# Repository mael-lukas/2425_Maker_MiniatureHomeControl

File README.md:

Miniature Home control

Maker 2024-2025 - Miniature Home control
========================================

Project overview

Introduction
------------

This project was carried out as part of the Maker option at ENSEA. The idea was to create a miniature home that could house a small animal with a bunch of actuated parts  
(doors, lights, food dispenser...) that could be activated remotely.  
Design-wise the house is inspired by typical doll house designs and modern houses:

Below is the architectural diagram that sums up all the features that were to be included in the house at the start of the project:

CAD
---

This project involved a lot of CAD. A significant part was the modeling of the whole house. The goal was to make the house out of wood using the laser cutter.  
Thus the model needed to be able to be separated in several parts to be cut on a flat sheet

All the furnitures to be placed in the house were also 3D modeled by myself (except the chair I downloaded it online). They were then 3D printed.

PCB
---

Every PCBs in this project were designed on KiCAD and manufactured by JLCPCB.  
This project needed two PCBs: one main unit would be wired to every actuatable parts in the house.  
Thus, it is mainly comprised of sockets to wire to every motors, lights, TV...

The second PCB is the controller of the house to actuate remotely every part of the house. Thus it is mainly comprised of buttons to look like a run-of-the-mill remote:

Assembly
--------

After laser cutting the wood the house was assembled, some furnitures were also placed inside:

The assembly part also involved a lot of wiring. I made custom wires for the power supply to power the main unit, a LiPo battery for the controller  
and several wires for motors and lights in the house:

Programming
-----------

The code was written  in C language on STM32 CubeIDE. It is devised according to this diagram:

I wrote a working code for the LCD screen (for the TV), servo motors, Neopixel LEDs and the MP3 module. I did not have time to test the code for the HC-05 bluetooth module.  
The whole code can be found in the GitHub repository (as well as every other resources of the project)

Final word
----------

I did not have the time to finish the project so only the house, the PCBs and the lights and doors are implemented but I still had a great time doing this project and participating in Maker.

### Short video

Here is a short [video](https://www.youtube.com/watch?v=WIeOZKU2mvY&t=1s) (in French) to sum up the project and my views on the Maker option

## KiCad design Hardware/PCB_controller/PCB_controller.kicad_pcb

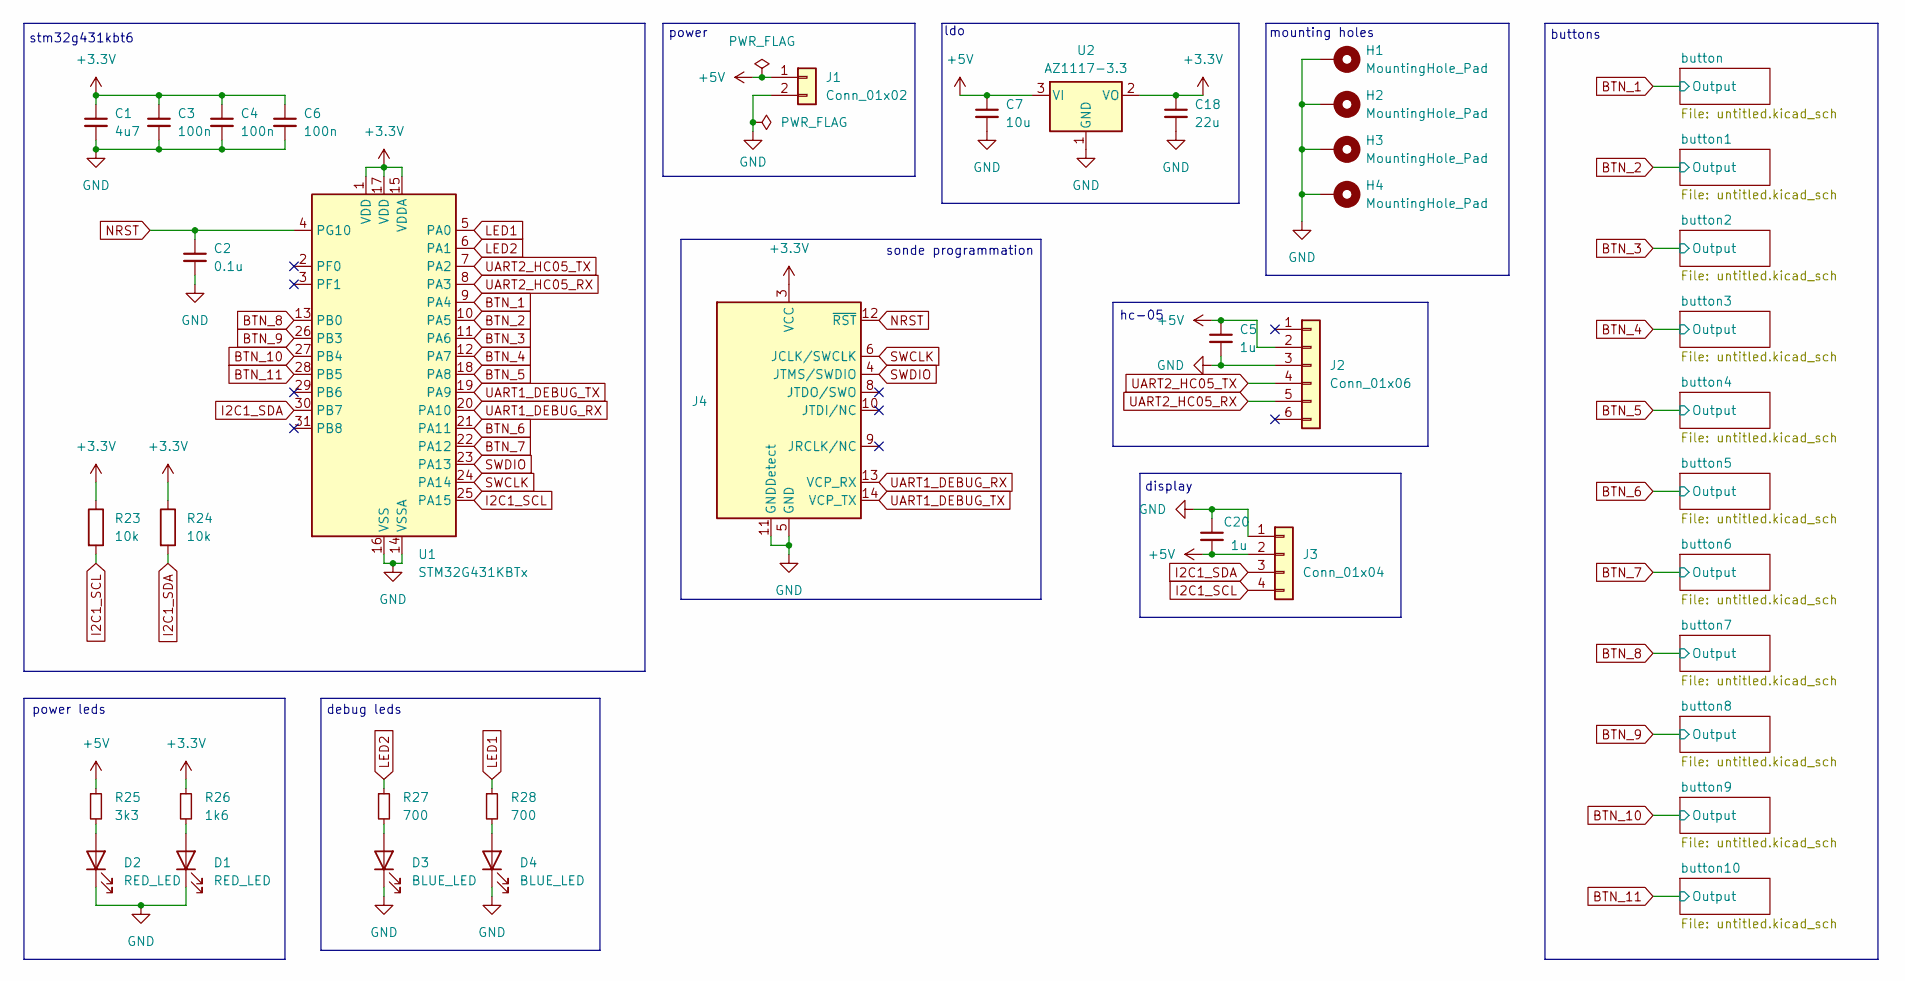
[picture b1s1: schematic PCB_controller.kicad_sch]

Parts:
C1: 4u7; C_0603_1608Metric
C2: 0.1u; C_0402_1005Metric_Pad0.74x0.62mm_HandSolder
C3, C4, C6: 100n; C_0402_1005Metric_Pad0.74x0.62mm_HandSolder
C5, C20: 1u; C_0603_1608Metric
C7: 10u; C_0603_1608Metric
C18: 22u; C_Elec_5x5.4
D1, D2: RED_LED; LED_0603_1608Metric; MPN 150060RS55040
D3, D4: BLUE_LED; LED_0603_1608Metric; MPN 150060BS55040
H1, H2, H3, H4: MountingHole_Pad; MountingHole_3.2mm_M3_Pad_Via
J1: Conn_01x02; JST_EH_B2B-EH-A_1x02_P2.50mm_Vertical
J2: Conn_01x06; JST_EH_B6B-EH-A_1x06_P2.50mm_Vertical
J3: Conn_01x04; JST_EH_B4B-EH-A_1x04_P2.50mm_Vertical
J4: Conn_ST_STDC14; PinHeader_2x07_P1.27mm_Vertical_SMD
R23, R24: 10k; R_0402_1005Metric_Pad0.72x0.64mm_HandSolder
R25: 3k3; R_0402_1005Metric_Pad0.72x0.64mm_HandSolder
R26: 1k6; R_0402_1005Metric_Pad0.72x0.64mm_HandSolder
R27, R28: 700; R_0402_1005Metric_Pad0.72x0.64mm_HandSolder
U1: STM32G431KBTx; LQFP-32_7x7mm_P0.8mm
U2: AZ1117-3.3; SOT-223-3_TabPin2; MPN AZ1117CH2-3.3TRG1

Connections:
+3.3V: C1.1, C3.1, C4.1, C6.1, C18.1, J4.3 (VCC), R23.1, R24.1, R26.1, U1.1 (VDD), U1.15 (VDDA), U1.17 (VDD), U2.2 (VO); also elsewhere on the board
+5V: C5.1, C7.1, C20.2, J1.1, J2.2, J3.2, R25.1, U2.3 (VI)
BTN_1: U1.9 (PA4); also elsewhere on the board
BTN_2: U1.10 (PA5); also elsewhere on the board
BTN_3: U1.11 (PA6); also elsewhere on the board
BTN_4: U1.12 (PA7); also elsewhere on the board
BTN_5: U1.18 (PA8); also elsewhere on the board
BTN_6: U1.21 (PA11); also elsewhere on the board
BTN_7: U1.22 (PA12); also elsewhere on the board
BTN_8: U1.13 (PB0); also elsewhere on the board
BTN_9: U1.26 (PB3); also elsewhere on the board
BTN_10: U1.27 (PB4); also elsewhere on the board
BTN_11: U1.28 (PB5); also elsewhere on the board
GND: C1.2, C2.2, C3.2, C4.2, C5.2, C6.2, C7.2, C18.2, C20.1, D1.1 (K), D2.1 (K), D3.1 (K), D4.1 (K), H1.1, H2.1, H3.1, H4.1, J1.2, J2.3, J3.1, J4.5 (GND), J4.7 (GND), J4.11 (GNDDetect), U1.14 (VSSA), U1.16 (VSS), U1.32 (VSS), U2.1 (GND); also elsewhere on the board
I2C1_SCL: J3.4, R23.2, U1.25 (PA15)
I2C1_SDA: J3.3, R24.2, U1.30 (PB7)
LED1: R28.1, U1.5 (PA0)
LED2: R27.1, U1.6 (PA1)
NRST: C2.1, J4.12 (~RST), U1.4 (PG10)
unnamed: D1.2 (A), R26.2
unnamed: D2.2 (A), R25.2
unnamed: D3.2 (A), R27.2
unnamed: D4.2 (A), R28.2
SWCLK: J4.6 (JCLK/SWCLK), U1.24 (PA14)
SWDIO: J4.4 (JTMS/SWDIO), U1.23 (PA13)
UART1_DEBUG_RX: J4.13 (VCP_RX), U1.20 (PA10)
UART1_DEBUG_TX: J4.14 (VCP_TX), U1.19 (PA9)
UART2_HC05_RX: J2.5, U1.8 (PA3)
UART2_HC05_TX: J2.4, U1.7 (PA2)

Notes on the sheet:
mounting holes
ldo
buttons
stm32g431kbt6
power
sonde programmation
debug leds
display
power leds
hc-05

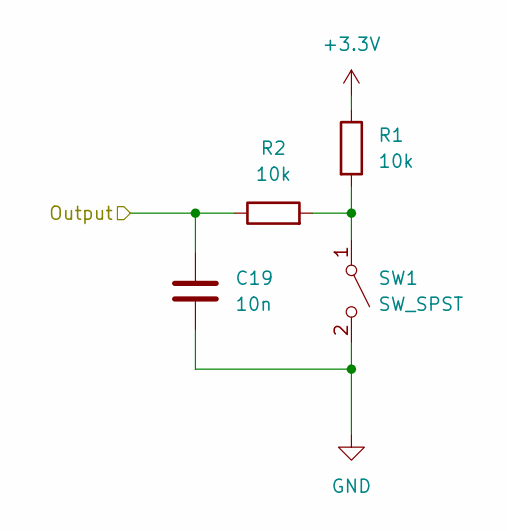
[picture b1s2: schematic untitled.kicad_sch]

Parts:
C19: 10n; C_0402_1005Metric_Pad0.74x0.62mm_HandSolder
R1, R2: 10k; R_0402_1005Metric_Pad0.72x0.64mm_HandSolder
SW1: SW_SPST; botan

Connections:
+3.3V: R1.1; also elsewhere on the board
BTN_1: C19.1, R2.1; also elsewhere on the board
GND: C19.2, SW1.2 (B); also elsewhere on the board
unnamed: R1.2, R2.2, SW1.1 (A)

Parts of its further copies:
C8, C9, C10, C11, C12, C13, C14, C15, C16, C17: 10n; C_0402_1005Metric_Pad0.74x0.62mm_HandSolder
R3, R4, R5, R6, R7, R8, R9, R10, R11, R12, R13, R14, R15, R16, R17, R18, R19, R20, R21, R22: 10k; R_0402_1005Metric_Pad0.72x0.64mm_HandSolder
SW2, SW3, SW4, SW5, SW6, SW7, SW8, SW9, SW10, SW11: SW_SPST; botan

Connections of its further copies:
+3.3V: R4.1, R6.1, R8.1, R10.1, R12.1, R14.1, R16.1, R18.1, R20.1, R22.1; also elsewhere on the board
BTN_2: C8.1, R3.1; also elsewhere on the board
BTN_3: C9.1, R5.1; also elsewhere on the board
BTN_4: C10.1, R7.1; also elsewhere on the board
BTN_5: C11.1, R9.1; also elsewhere on the board
BTN_6: C12.1, R11.1; also elsewhere on the board
BTN_7: C13.1, R13.1; also elsewhere on the board
BTN_8: C14.1, R15.1; also elsewhere on the board
BTN_9: C15.1, R17.1; also elsewhere on the board
BTN_10: C16.1, R19.1; also elsewhere on the board
BTN_11: C17.1, R21.1; also elsewhere on the board
GND: C8.2, C9.2, C10.2, C11.2, C12.2, C13.2, C14.2, C15.2, C16.2, C17.2, SW2.2 (B), SW3.2 (B), SW4.2 (B), SW5.2 (B), SW6.2 (B), SW7.2 (B), SW8.2 (B), SW9.2 (B), SW10.2 (B), SW11.2 (B); also elsewhere on the board
unnamed: R3.2, R4.2, SW2.1 (A)
unnamed: R5.2, R6.2, SW3.1 (A)
unnamed: R7.2, R8.2, SW4.1 (A)
unnamed: R9.2, R10.2, SW5.1 (A)
unnamed: R11.2, R12.2, SW6.1 (A)
unnamed: R13.2, R14.2, SW7.1 (A)
unnamed: R15.2, R16.2, SW8.1 (A)
unnamed: R17.2, R18.2, SW9.1 (A)
unnamed: R19.2, R20.2, SW10.1 (A)
unnamed: R21.2, R22.2, SW11.1 (A)

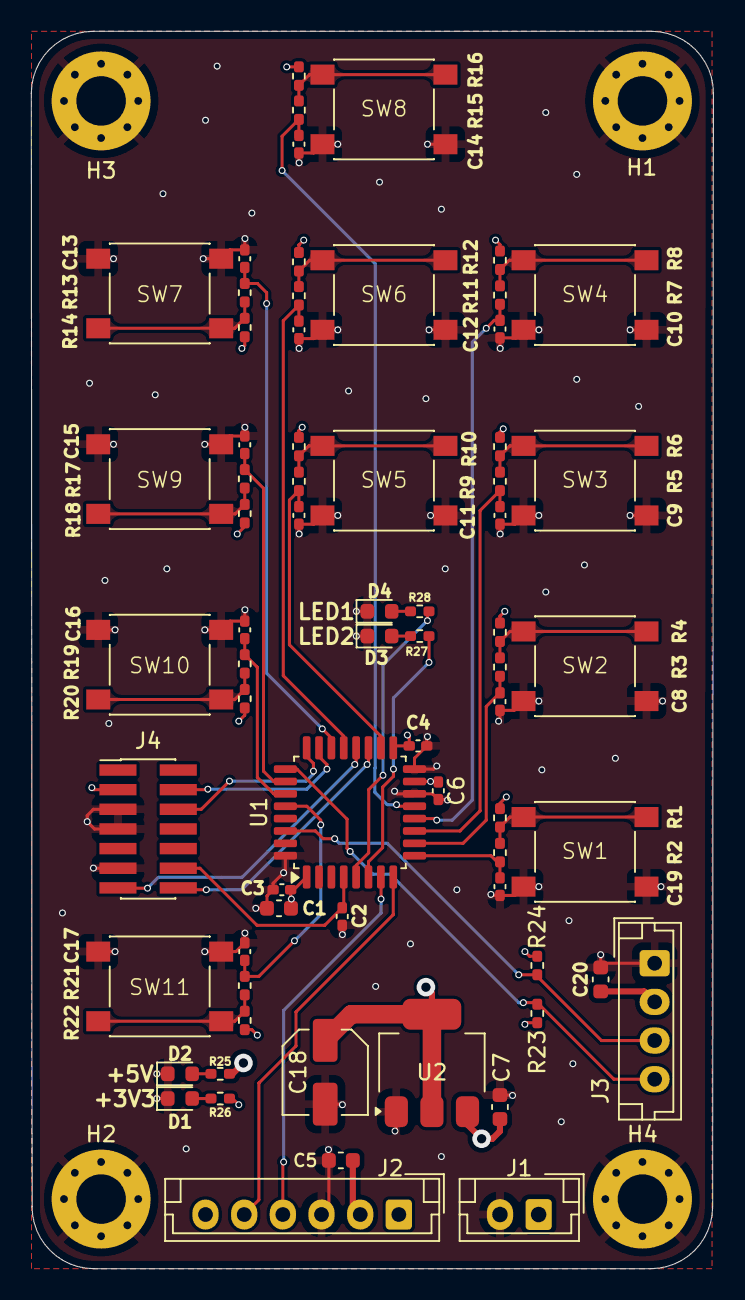
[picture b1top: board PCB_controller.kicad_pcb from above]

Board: 4 copper layers, 44.1 x 80.0 mm, 73 parts (0 on the bottom side), 40 nets.

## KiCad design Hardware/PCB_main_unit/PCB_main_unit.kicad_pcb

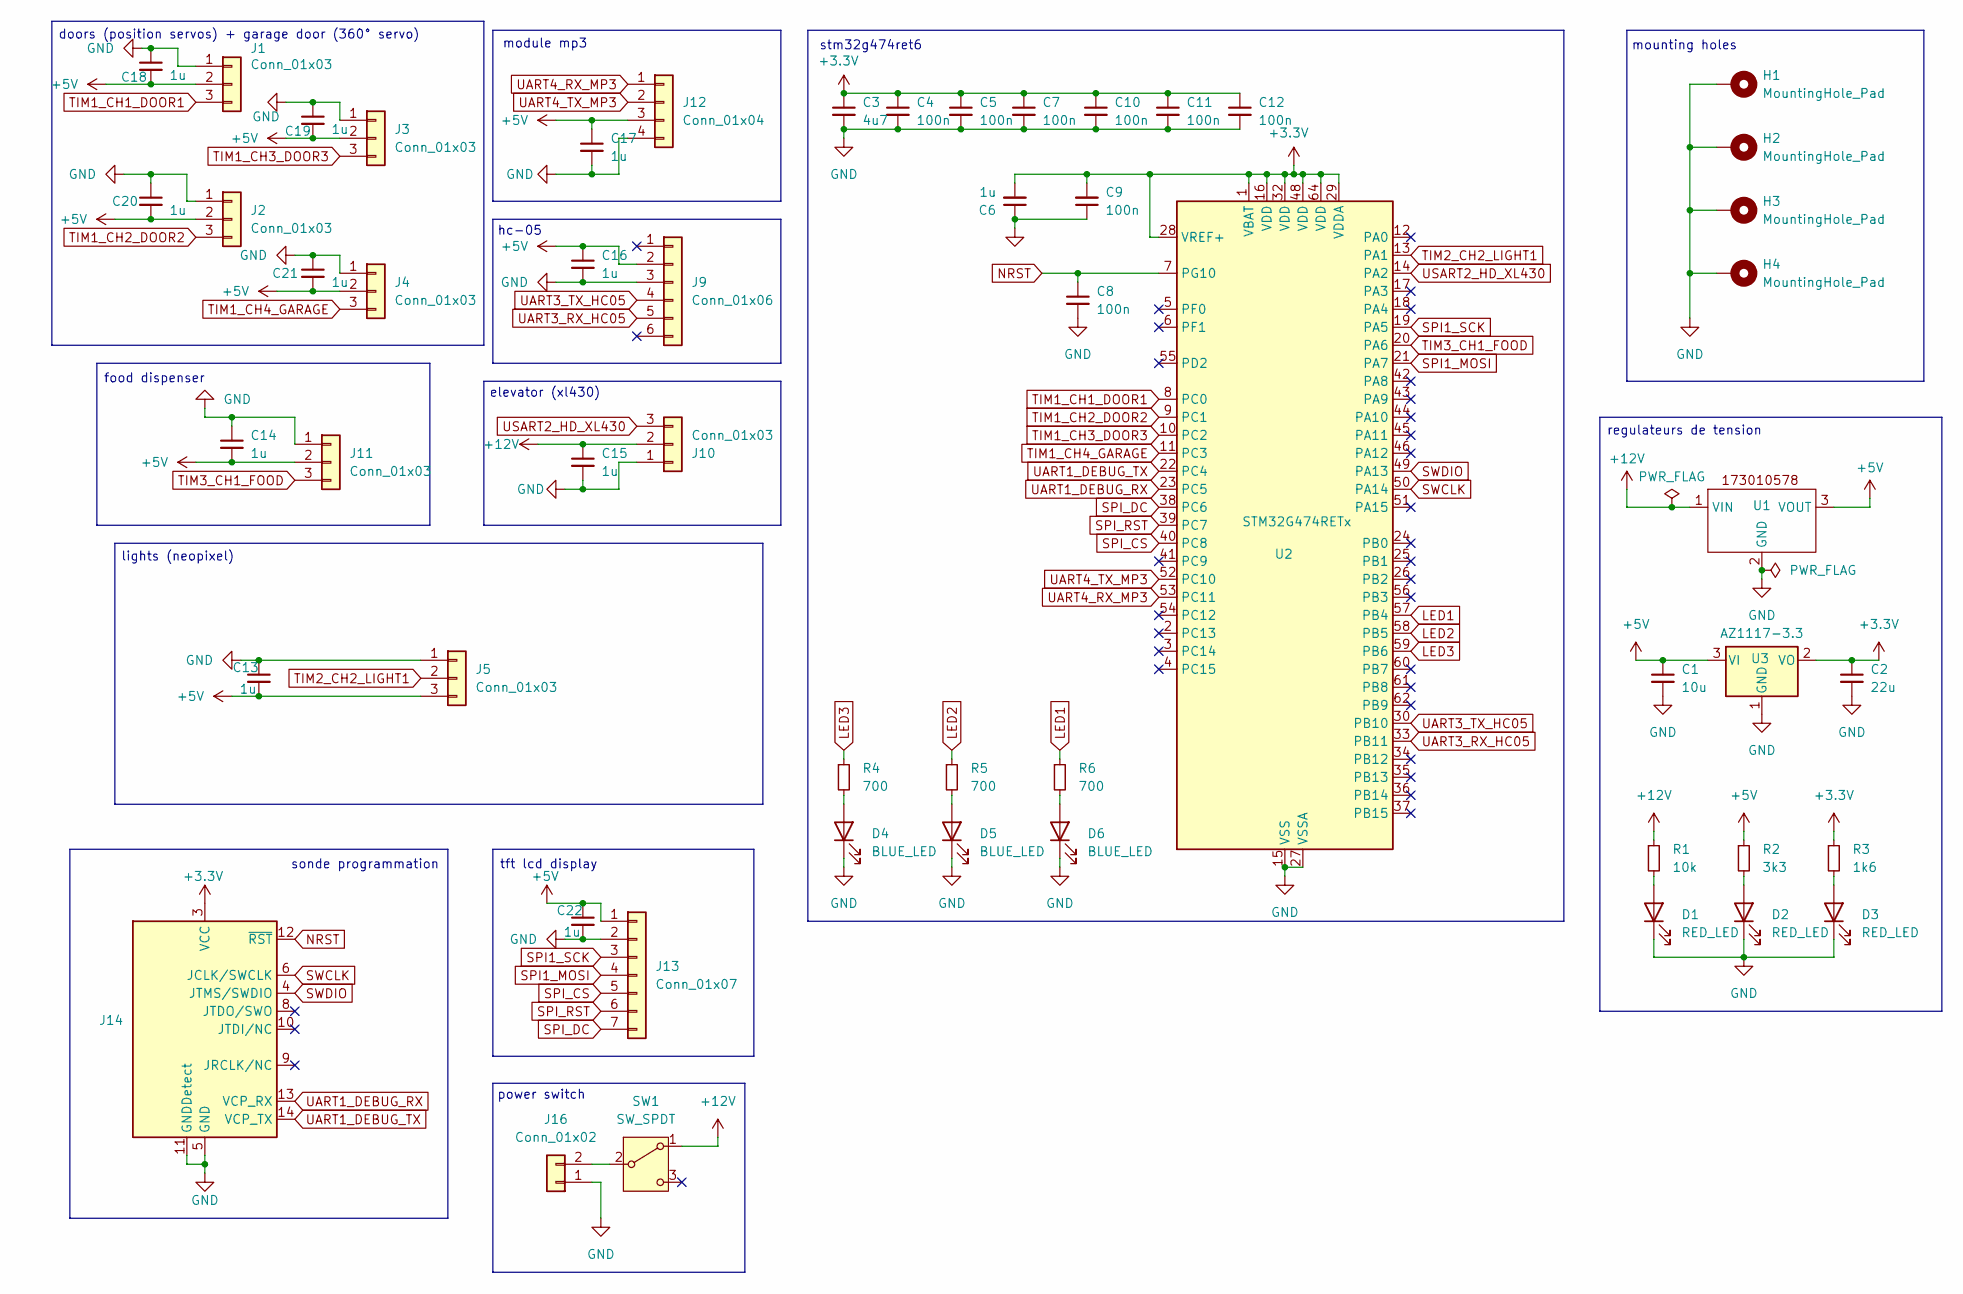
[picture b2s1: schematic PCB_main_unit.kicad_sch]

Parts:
C1: 10u; C_0603_1608Metric
C2: 22u; C_Elec_5x5.4
C3: 4u7; C_0603_1608Metric
C4, C5, C7, C8, C9, C10, C11, C12: 100n; C_0402_1005Metric_Pad0.74x0.62mm_HandSolder
C6, C13, C14, C15, C16, C17, C18, C19, C20, C21, C22: 1u; C_0603_1608Metric
D1, D2, D3: RED_LED; LED_0603_1608Metric; MPN 150060RS55040
D4, D5, D6: BLUE_LED; LED_0603_1608Metric; MPN 150060BS55040
H1, H2, H3, H4: MountingHole_Pad; MountingHole_3.2mm_M3_Pad_Via
J1, J2, J3, J4, J5, J10, J11: Conn_01x03; JST_EH_B3B-EH-A_1x03_P2.50mm_Vertical
J9: Conn_01x06; JST_EH_B6B-EH-A_1x06_P2.50mm_Vertical
J12: Conn_01x04; JST_EH_B4B-EH-A_1x04_P2.50mm_Vertical
J13: Conn_01x07; JST_EH_B7B-EH-A_1x07_P2.50mm_Vertical
J14: Conn_ST_STDC14; PinHeader_2x07_P1.27mm_Vertical_SMD
J16: Conn_01x02; AMASS_XT60-M_1x02_P7.20mm_Vertical
R1: 10k; R_0402_1005Metric_Pad0.72x0.64mm_HandSolder
R2: 3k3; R_0402_1005Metric_Pad0.72x0.64mm_HandSolder
R3: 1k6; R_0402_1005Metric_Pad0.72x0.64mm_HandSolder
R4, R5, R6: 700; R_0402_1005Metric_Pad0.72x0.64mm_HandSolder
SW1: SW_SPDT; power_switch; MPN 472123010111
U1: 173010578; MPN 173010578
U2: STM32G474RETx; LQFP-64_10x10mm_P0.5mm
U3: AZ1117-3.3; SOT-223-3_TabPin2; MPN AZ1117CH2-3.3TRG1

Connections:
+3.3V: C2.1, C3.1, C4.1, C5.1, C6.2, C7.1, C9.2, C10.1, C11.1, C12.1, J14.3 (VCC), R3.1, U2.1 (VBAT), U2.16 (VDD), U2.28 (VREF+), U2.29 (VDDA), U2.32 (VDD), U2.48 (VDD), U2.64 (VDD), U3.2 (VO)
+5V: C1.1, C13.2, C14.2, C16.1, C17.1, C18.2, C19.2, C20.2, C21.2, C22.1, J1.2, J2.2, J3.2, J4.2, J5.3, J9.2, J11.2, J12.3, J13.1, R2.1, U1.3 (VOUT), U3.3 (VI)
+12V: C15.1, J10.2, R1.1, SW1.1 (A), U1.1 (VIN)
GND: C1.2, C2.2, C3.2, C4.2, C5.2, C6.1, C7.2, C8.2, C9.1, C10.2, C11.2, C12.2, C13.1, C14.1, C15.2, C16.2, C17.2, C18.1, C19.1, C20.1, C21.1, C22.2, D1.1 (K), D2.1 (K), D3.1 (K), D4.1 (K), D5.1 (K), D6.1 (K), H1.1, H2.1, H3.1, H4.1, J1.1, J2.1, J3.1, J4.1, J5.1, J9.3, J10.1, J11.1, J12.4, J13.2, J14.5 (GND), J14.7 (GND), J14.11 (GNDDetect), J16.1, U1.2 (GND), U2.15 (VSS), U2.27 (VSSA), U2.31 (VSS), U2.47 (VSS), U2.63 (VSS), U3.1 (GND)
LED1: R6.1, U2.57 (PB4)
LED2: R5.1, U2.58 (PB5)
LED3: R4.1, U2.59 (PB6)
NRST: C8.1, J14.12 (~RST), U2.7 (PG10)
unnamed: D1.2 (A), R1.2
unnamed: D2.2 (A), R2.2
unnamed: D3.2 (A), R3.2
unnamed: D4.2 (A), R4.2
unnamed: D5.2 (A), R5.2
unnamed: D6.2 (A), R6.2
unnamed: J16.2, SW1.2 (B)
SPI1_MOSI: J13.4, U2.21 (PA7)
SPI1_SCK: J13.3, U2.19 (PA5)
SPI_CS: J13.5, U2.40 (PC8)
SPI_DC: J13.7, U2.38 (PC6)
SPI_RST: J13.6, U2.39 (PC7)
SWCLK: J14.6 (JCLK/SWCLK), U2.50 (PA14)
SWDIO: J14.4 (JTMS/SWDIO), U2.49 (PA13)
TIM1_CH1_DOOR1: J1.3, U2.8 (PC0)
TIM1_CH2_DOOR2: J2.3, U2.9 (PC1)
TIM1_CH3_DOOR3: J3.3, U2.10 (PC2)
TIM1_CH4_GARAGE: J4.3, U2.11 (PC3)
TIM2_CH2_LIGHT1: J5.2, U2.13 (PA1)
TIM3_CH1_FOOD: J11.3, U2.20 (PA6)
UART1_DEBUG_RX: J14.13 (VCP_RX), U2.23 (PC5)
UART1_DEBUG_TX: J14.14 (VCP_TX), U2.22 (PC4)
UART3_RX_HC05: J9.5, U2.33 (PB11)
UART3_TX_HC05: J9.4, U2.30 (PB10)
UART4_RX_MP3: J12.1, U2.53 (PC11)
UART4_TX_MP3: J12.2, U2.52 (PC10)
USART2_HD_XL430: J10.3, U2.14 (PA2)

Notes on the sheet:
elevator (xl430)
tft lcd display
doors (position servos) + garage door (360° servo)
hc-05
stm32g474ret6
lights (neopixel)
sonde programmation
module mp3
food dispenser
power switch
mounting holes
regulateurs de tension

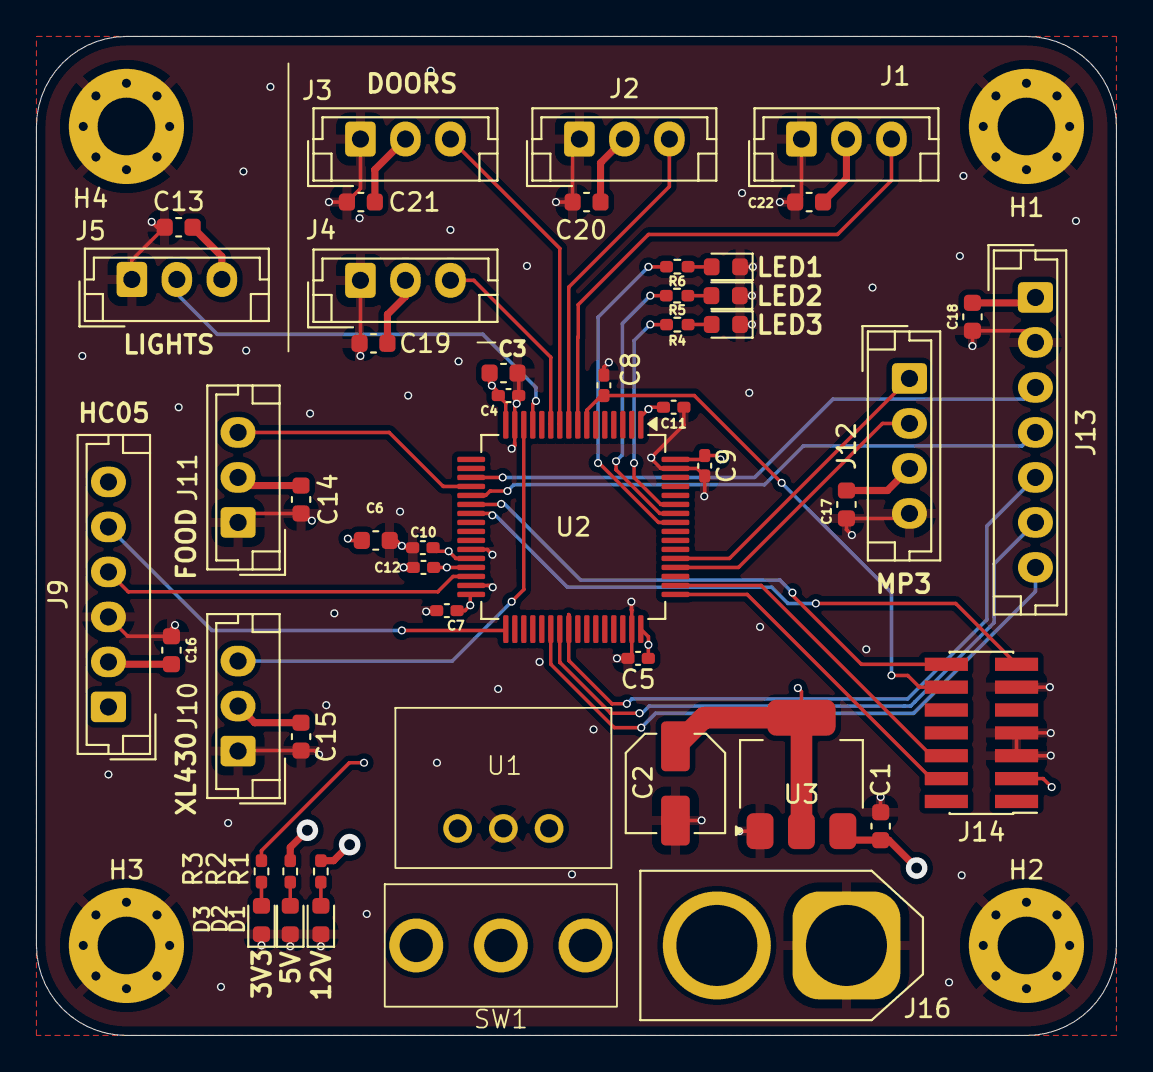
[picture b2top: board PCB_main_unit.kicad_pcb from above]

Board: 4 copper layers, 60.0 x 55.5 mm, 54 parts (0 on the bottom side), 35 nets.

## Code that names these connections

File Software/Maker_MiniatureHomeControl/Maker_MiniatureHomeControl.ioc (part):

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Mcu.Name=STM32G474R(B-C-E)Tx
Mcu.Package=LQFP64
Mcu.UserName=STM32G474RETx
PA1.GPIOParameters=GPIO_Label
PA1.GPIO_Label=TIM2_CH2 (light1)
PA1.Signal=S_TIM2_CH2
PA13.Mode=Serial_Wire
PA13.Signal=SYS_JTMS-SWDIO
PA14.Mode=Serial_Wire
PA14.Signal=SYS_JTCK-SWCLK
PA2.GPIOParameters=GPIO_Label
PA2.GPIO_Label=USART2_TX (xl430)
PA2.Mode=Half_duplex(single_wire_mode)
PA2.Signal=USART2_TX
PA5.Mode=Simplex_Bidirectional_Master
PA5.Signal=SPI1_SCK
PA6.GPIOParameters=GPIO_Label
PA6.GPIO_Label=TIM3_CH1 (food)
PA6.Signal=S_TIM3_CH1
PA7.Mode=Simplex_Bidirectional_Master
PA7.Signal=SPI1_MOSI
PB10.GPIOParameters=GPIO_Label
PB10.GPIO_Label=USART3_TX (hc05)
PB10.Mode=Asynchronous
PB10.Signal=USART3_TX
PB11.GPIOParameters=GPIO_Label
PB11.GPIO_Label=USART3_RX (hc05)
PB11.Mode=Asynchronous
PB11.Signal=USART3_RX
PB4.GPIOParameters=GPIO_Label
PB4.GPIO_Label=LED1
PB4.Signal=GPIO_Output
PB5.GPIOParameters=GPIO_Label
PB5.GPIO_Label=LED2
PB5.Signal=GPIO_Output
PB6.GPIOParameters=GPIO_Label
PB6.GPIO_Label=LED3
PB6.Signal=GPIO_Output
PC0.GPIOParameters=GPIO_Label
PC0.GPIO_Label=TIM1_CH1 (door1)
PC0.Signal=S_TIM1_CH1
PC1.GPIOParameters=GPIO_Label
PC1.GPIO_Label=TIM1_CH2 (door2)
PC1.Signal=S_TIM1_CH2
PC10.GPIOParameters=GPIO_Label
PC10.GPIO_Label=UART4_TX (mp3)
PC10.Mode=Asynchronous
PC10.Signal=UART4_TX
PC11.GPIOParameters=GPIO_Label
PC11.GPIO_Label=UART4_RX (mp3)
PC11.Mode=Asynchronous
PC11.Signal=UART4_RX
PC2.GPIOParameters=GPIO_Label
PC2.GPIO_Label=TIM1_CH3 (door3)
PC2.Signal=S_TIM1_CH3
PC3.GPIOParameters=GPIO_Label
PC3.GPIO_Label=TIM1_CH4 (garage)
PC3.Signal=S_TIM1_CH4
PC4.GPIOParameters=GPIO_Label
PC4.GPIO_Label=USART1_TX (sonde)
PC4.Mode=Asynchronous
PC4.Signal=USART1_TX
PC5.GPIOParameters=GPIO_Label
PC5.GPIO_Label=USART1_RX (sonde)
PC5.Mode=Asynchronous
PC5.Signal=USART1_RX
PC6.GPIOParameters=GPIO_Label
PC6.GPIO_Label=SPI_DC
PC6.Signal=GPIO_Output
PC7.GPIOParameters=GPIO_Label
PC7.GPIO_Label=SPI_RST
PC7.Signal=GPIO_Output
PC8.GPIOParameters=GPIO_Label
PC8.GPIO_Label=SPI_CS
PC8.Signal=GPIO_Output
RCC.HSE_VALUE=8000000
RCC.SYSCLKFreq_VALUE=16000000
board=custom

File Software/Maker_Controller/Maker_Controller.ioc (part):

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Mcu.Name=STM32G431K(6-8-B)Tx
Mcu.Package=LQFP32
Mcu.UserName=STM32G431KBTx
PA0.GPIOParameters=GPIO_Label
PA0.GPIO_Label=LED1
PA0.Signal=GPIO_Output
PA1.GPIOParameters=GPIO_Label
PA1.GPIO_Label=LED2
PA1.Signal=GPIO_Output
PA10.GPIOParameters=GPIO_Label
PA10.GPIO_Label=USART1_RX (sonde)
PA10.Mode=Asynchronous
PA10.Signal=USART1_RX
PA11.GPIOParameters=GPIO_Label
PA11.GPIO_Label=BTN6
PA11.Signal=GPIO_Input
PA12.GPIOParameters=GPIO_Label
PA12.GPIO_Label=BTN7
PA12.Signal=GPIO_Input
PA13.Mode=Serial_Wire
PA13.Signal=SYS_JTMS-SWDIO
PA14.Mode=Serial_Wire
PA14.Signal=SYS_JTCK-SWCLK
PA15.Mode=I2C
PA15.Signal=I2C1_SCL
PA2.GPIOParameters=GPIO_Label
PA2.GPIO_Label=USART2_TX (hc05)
PA2.Mode=Asynchronous
PA2.Signal=USART2_TX
PA3.GPIOParameters=GPIO_Label
PA3.GPIO_Label=USART2_RX (hc05)
PA3.Mode=Asynchronous
PA3.Signal=USART2_RX
PA4.GPIOParameters=GPIO_Label
PA4.GPIO_Label=BTN1
PA4.Signal=GPIO_Input
PA5.GPIOParameters=GPIO_Label
PA5.GPIO_Label=BTN2
PA5.Signal=GPIO_Input
PA6.GPIOParameters=GPIO_Label
PA6.GPIO_Label=BTN3
PA6.Signal=GPIO_Input
PA7.GPIOParameters=GPIO_Label
PA7.GPIO_Label=BTN4
PA7.Signal=GPIO_Input
PA8.GPIOParameters=GPIO_Label
PA8.GPIO_Label=BTN5
PA8.Signal=GPIO_Input
PA9.GPIOParameters=GPIO_Label
PA9.GPIO_Label=USART1_TX (sonde)
PA9.Mode=Asynchronous
PA9.Signal=USART1_TX
PB0.GPIOParameters=GPIO_Label
PB0.GPIO_Label=BTN8
PB0.Signal=GPIO_Input
PB3.GPIOParameters=GPIO_Label
PB3.GPIO_Label=BTN9
PB3.Signal=GPIO_Input
PB4.GPIOParameters=GPIO_Label
PB4.GPIO_Label=BTN10
PB4.Signal=GPIO_Input
PB5.GPIOParameters=GPIO_Label
PB5.GPIO_Label=BTN11
PB5.Signal=GPIO_Input
PB7.Mode=I2C
PB7.Signal=I2C1_SDA
RCC.HSE_VALUE=8000000
RCC.SYSCLKFreq_VALUE=16000000
board=custom

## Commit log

2025-01-20 created repo
2025-03-13 started schematic for pcbs
2025-03-13 finished main unit schematic
2025-03-15 started controller PCB
2025-03-15 finished controller pcb
2025-03-15 started main unit PCB
2025-03-15 j'ai rien a dire
2025-03-16 finished main unit PCB
2025-03-20 minor changes
2025-03-20 PINOUT for both uCs
2025-03-20 review sch
2025-03-20 applied changes
2025-03-20 generated gerbers and drill files
2025-03-23 update pcb
2025-03-23 export gerbers
2025-04-19 Project relevant datasheets
2025-04-19 deleted design inspirations
2025-04-19 Added design inspirations and relevant pictures
2025-04-19 C language software for house control
2025-04-19 added architectural diagram
2025-04-19 I forgor 1 datasheet
2025-04-19 updated archi diagram
2025-04-19 Rename Diagramme sans nom.drawio to archi diagram.drawio
2025-04-19 added archi diagram pdf format
2025-04-19 archi diagram jpg format
2025-04-19 added code architecture.drawio
2025-04-19 updated code architecture.drawio
2025-04-19 added code archi pdf format
2025-04-19 added code archi jpg format
2025-04-19 added CAD models of the projects
